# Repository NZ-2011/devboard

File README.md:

# 🔌 DevBoard — RP2040 Development Board

> A compact, open-source development board powered by the **Raspberry Pi RP2040** — featuring a 12 MHz crystal oscillator, onboard 3.3V regulation, QSPI Flash, SWD debug header, and 40 broken-out GPIO pins. Built for makers, students, and engineers who want full control.

---
## DEVBOARD
<!-- 📸 BOARD PHOTO: Replace the line below with your actual board photo -->

> 📷 *3D render and PCB layout available in `/assets/images/`*

# Purpose:
it is like an small computer that can fit in ur hand.you plug it in your computer or Laptop to test the prototype or product ypur makimg.it is used to conmect lights,sensors,mototrs according to the code you write.

# How to use it:
1- install the software.and open it.

2-plug the devboard in ur computer or laptop with a good USB cable (a normal cable will work too)

3-upload ur first program

4-connect real stuff. like LEDs,button etc
(always unplug USB before toiching wires)

# Why did i make it:
we all have to start somehwere to i thought to start my PCB,electronics journey from here.i could have selected something easy but where is the fun in that so i decided to make a devboard.and also during this i learned how to use kicad and how to make a PCB,and some ways to fix errors.

---

##  Features

- 🧠 **Microcontroller:** Raspberry Pi RP2040 (Dual-core ARM Cortex-M0+ @ up to 133MHz)
- 💾 **Flash Memory:** 2MB QSPI Flash (W25Q16)
- ⚡ **Power:** USB-C (USB 2.0, 14P) with onboard MCP1700-3300 LDO (3.3V output)
- 📌 **GPIO:** 40 pins broken out via dual 1×20 pin headers (GPIO0–GPIO29 + power/GND)
- 🔮 **Crystal:** 12 MHz external oscillator for accurate USB & timing
- 🔘 **Button:** 1× tactile push button (SW1 — Boot/User)
- 🛠️ **Debug:** 3-pin SWD header (J4) for hardware debugging
- 📐 **Form Factor:** Compact stick ~55mm × 21mm, Pico-compatible footprint
- 🎨 **PCB:** 2-layer green PCB with black pin headers
- 🔧 **Compatible with:** MicroPython, CircuitPython, Arduino IDE, C/C++ SDK

---

## 📐 SCHEMATIC

## PCB Design

## 3D imagine

## Magazine

| Left Header (J2) | Pin | Pin | Right Header (J3) |
|---|---|---|---|
| GPIO0 | 1 | 1 | GPIO16 |
| GPIO1 | 2 | 2 | GPIO17 |
| GPIO2 | 3 | 3 | GPIO18 |
| GPIO3 | 4 | 4 | GPIO19 |
| GPIO4 | 5 | 5 | GPIO20 |
| GPIO5 | 6 | 6 | GPIO21 |
| GPIO6 | 7 | 7 | GPIO22 |
| GPIO7 | 8 | 8 | GPIO23 |
| GPIO8 | 9 | 9 | GPIO24 |
| GPIO9 | 10 | 10 | GPIO25 |
| GPIO10 | 11 | 11 | GPIO26_ADC0 |
| GPIO11 | 12 | 12 | GPIO27_ADC1 |
| GPIO12 | 13 | 13 | GPIO28_ADC2 |
| GPIO13 | 14 | 14 | GPIO29_ADC3 |
| GPIO14 | 15 | 15 | VBUS (5V) |
| GPIO15 | 16 | 16 | 3V3 |
| RUN | 17 | 17 | GND |
| SWCLK | 18 | 18 | GND |
| SWDIO | 19 | 19 | GND |
| GND | 20 | 20 | GND |

> ⚠️ *GPIO26–29 are also ADC-capable. VBUS is 5V direct from USB — use with caution.*

---

##  Getting Started

### Prerequisites

- [Arduino IDE](https://www.arduino.cc/en/software) **or** [Thonny (MicroPython)](https://thonny.org/) **or** [VS Code + Pico SDK](https://www.raspberrypi.com/documentation/microcontrollers/c_sdk.html)
- USB-C cable
- [RP2040 Arduino Core by Earle Philhower](https://github.com/earlephilhower/arduino-pico) (if using Arduino IDE)

### Flash MicroPython

1. Hold the **BOOT button (SW1)** and plug in USB — the board mounts as a USB drive.
2. Download the latest [MicroPython UF2 for RP2040](https://micropython.org/download/rp2-pico/).
3. Drag and drop the `.uf2` file onto the drive — it reboots automatically.
4. Open **Thonny**, select `MicroPython (Raspberry Pi Pico)` as interpreter.
5. Run your first program:

```python
from machine import Pin
from time import sleep

led = Pin(25, Pin.OUT)  # Adjust to your onboard LED pin if present

while True:
    led.toggle()
    sleep(0.5)
```

### Flash with Arduino IDE

1. In Arduino IDE go to **File > Preferences** and add this URL to Board Manager:
   `https://github.com/earlephilhower/arduino-pico/releases/download/global/package_rp2040_index.json`
2. Go to **Tools > Board > Board Manager**, search `RP2040` and install.
3. Select **Raspberry Pi Pico** (or Generic RP2040) under Tools > Board.
4. Hold BOOT, plug in USB, then upload your sketch.

### SWD Debugging (Advanced)

Connect a **Picoprobe** or **J-Link** to the 3-pin SWD header (J4):

| J4 Pin | Signal |
|---|---|
| 1 | SWCLK |
| 2 | GND |
| 3 | SWDIO |

---

## 📁 Repository Structure

```
devboard/
├── hardware/
│   ├── schematic.pdf        # Full KiCad schematic export
│   ├── gerbers/             # Gerber files for PCB manufacturing
│   ├── bom.csv              # Bill of Materials
│   └── kicad/               # KiCad 6 source files (.kicad_sch, .kicad_pcb)
├── firmware/
│   └── examples/            # MicroPython & Arduino example sketches
├── assets/
│   └── images/              # Board photos, 3D renders, pinout diagrams
├── docs/
│   └── getting-started.md   # Detailed setup guide
├── LICENSE-HARDWARE         # CERN OHL v2-S
├── LICENSE-FIRMWARE         # MIT
└── README.md
```

---

## 🔧 Hardware Files

| File | Description |
|---|---|
| `hardware/schematic.pdf` | Full circuit schematic (KiCad 6.0) |
| `hardware/gerbers/` | Gerber + drill files — tested with JLCPCB & PCBWay |
| `hardware/bom.csv` | Full BOM: W25Q16, MCP1700-3300, 12MHz crystal, passives |
| `hardware/kicad/` | Editable KiCad source files |

**Key ICs used:**
- `U1` — RP2040 (Raspberry Pi)
- `U2` — MCP1700-3300TT (3.3V LDO, 250mA)
- `U4` — W25Q16 (2MB QSPI Flash)
- `Y1` — 12 MHz Crystal Oscillator

---

> 💡 Have an idea? [Open a feature request](https://github.com/NZ-2011/devboard/issues/new?template=feature_request.md)

##Createdwith help of hackclub tutorial.
---

## Contributing

Contributions are what make open source amazing! Here's how you can help:

### Reporting Bugs
1. Check if the issue exists in [Issues](https://github.com/NZ-2011/devboard/issues)
2. Open a new issue with your OS, toolchain version, steps to reproduce, and expected vs actual behavior.

### Submitting Hardware Changes
1. Fork the repo
2. Edit in **KiCad** (same version used for this project)
3. Export updated Gerbers + schematic PDF
4. Submit a Pull Request with a clear description

### Submitting Firmware / Code
1. Fork the repo
2. Create a branch: `git checkout -b feature/your-feature-name`
3. Commit: `git commit -m "Add: description of change"`
4. Push and open a Pull Request

Look for [`good first issue`](https://github.com/NZ-2011/devboard/labels/good%20first%20issue) tags for beginner-friendly tasks!

---

## 📜 License

This project uses two licenses:

- **Firmware & Software** → [MIT License](LICENSE-FIRMWARE) — free to use, modify, and distribute with credit.
- **Hardware (PCB, Schematics)** → [CERN Open Hardware Licence v2 - Strongly Reciprocal](LICENSE-HARDWARE) — open hardware; modifications must also stay open.

---

## 🙌 Acknowledgements

- [Raspberry Pi Foundation](https://www.raspberrypi.com/) for the RP2040 chip and documentation
- [KiCad EDA](https://www.kicad.org/) for open-source PCB design tools
---

<p align="center">⭐ If you find this useful, please star the repo — it helps others discover it!</p>

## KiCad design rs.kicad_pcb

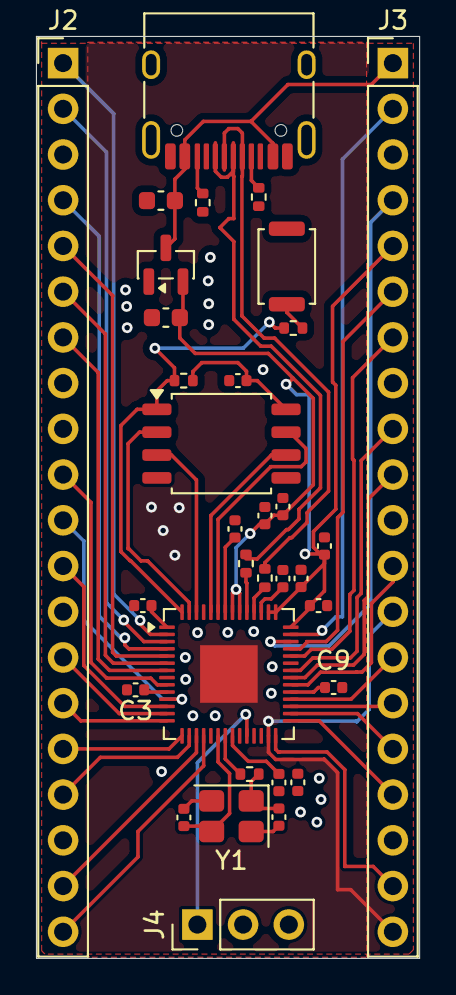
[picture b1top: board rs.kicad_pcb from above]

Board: 2 copper layers, 21.3 x 51.2 mm, 33 parts (0 on the bottom side), 48 nets.

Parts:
C1, C10: 1uF; C_0402_1005Metric
C2, C3, C4, C5, C6, C7, C8, C9, C11, C12, C17: 0.1uF; C_0402_1005Metric
C13, C14: 10uF; C_0603_1608Metric
C15, C16: 33pF; C_0402_1005Metric
J1: USB_C_Receptacle_USB2.0_14P; USB_C_Receptacle_HRO_TYPE-C-31-M-12
J2, J3: Conn_01x20; PinHeader_1x20_P2.54mm_Vertical
J4: Conn_01x03; PinHeader_1x03_P2.54mm_Vertical
R1, R2: 5.1K; R_0402_1005Metric
R3, R4: 27; R_0402_1005Metric
R5, R6: 1K; R_0402_1005Metric
R7: 10K; R_0402_1005Metric
SW1: SW_Push; SW_Push_SPST_NO_Alps_SKRK
U1: RP2040; QFN-56-1EP_7x7mm_P0.4mm_EP3.2x3.2mm
U2: MCP1700x-330xxTT; SOT-23
U4: W25Q16JVUXIQ TR; SOIC-8_5.3x5.3mm_P1.27mm
Y1: 12 MHz; Crystal_SMD_3225-4Pin_3.2x2.5mm

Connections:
+1V1: C10.1, C11.1, C12.1, U1.23 (DVDD), U1.45 (VREG_VOUT), U1.50 (DVDD)
+3V3: C1.1, C2.1, C3.1, C4.1, C5.1, C6.1, C7.1, C8.1, C9.1, C14.1, C17.1, J3.5, R7.1, U1.1 (IOVDD), U1.10 (IOVDD), U1.22 (IOVDD), U1.33 (IOVDD), U1.42 (IOVDD), U1.43 (ADC_AVDD), U1.44 (VREG_VIN), U1.48 (USB_VDD), U1.49 (IOVDD), U2.2 (VO), U4.8 (VCC)
/GPIO0: J2.1, U1.2 (GPIO0)
/GPIO1: J2.2, U1.3 (GPIO1)
/GPIO2: J2.4, U1.4 (GPIO2)
/GPIO3: J2.5, U1.5 (GPIO3)
/GPIO4: J2.6, U1.6 (GPIO4)
/GPIO5: J2.7, U1.7 (GPIO5)
/GPIO6: J2.9, U1.8 (GPIO6)
/GPIO7: J2.10, U1.9 (GPIO7)
/GPIO8: J2.11, U1.11 (GPIO8)
/GPIO9: J2.12, U1.12 (GPIO9)
/GPIO10: J2.14, U1.13 (GPIO10)
/GPIO11: J2.15, U1.14 (GPIO11)
/GPIO12: J2.16, U1.15 (GPIO12)
/GPIO13: J2.17, U1.16 (GPIO13)
/GPIO14: J2.19, U1.17 (GPIO14)
/GPIO15: J2.20, U1.18 (GPIO15)
/GPIO17: J3.19, U1.28 (GPIO17)
/GPIO18: J3.17, U1.29 (GPIO18)
/GPIO19: J3.16, U1.30 (GPIO19)
/GPIO20: J3.15, U1.31 (GPIO20)
/GPIO21: J3.14, U1.32 (GPIO21)
/GPIO22: J3.12, U1.34 (GPIO22)
/GPIO23: J3.10, U1.35 (GPIO23)
/GPIO24: J3.9, U1.36 (GPIO24)
/GPIO26_ADC0: J3.7, U1.38 (GPIO26/ADC0)
/GPIO27_ADC1: J3.6, U1.39 (GPIO27/ADC1)
/GPIO28_ADC2: J3.4, U1.40 (GPIO28/ADC2)
/GPIO29_ADC3: J3.2, U1.41 (GPIO29/ADC3)
/QSPI_SCLK: U1.52 (QSPI_SCLK), U4.6 (CLK)
/QSPI_SD1: U1.55 (QSPI_SD1), U4.2 (DO/IO_{1})
/QSPI_SD2: U1.54 (QSPI_SD2), U4.3 (~WP/IO_{2})
/QSPI_SD3: U1.51 (QSPI_SD3), U4.7 (~HOLD/~RESET/IO_{3})
/QSPI_SS: R6.1, R7.2, U1.56 (~QSPI_SS), U4.1 (~CS)
/SWCLK: J4.1, U1.24 (SWCLK)
/USB_D+: J1.A6 (D+), J1.B6 (D+), R3.1
/USB_D-: J1.A7 (D-), J1.B7 (D-), R4.1
/XIN: C15.2, U1.20 (XIN), Y1.3
/XOUT: R5.2, U1.21 (XOUT)
GND: C1.2, C2.2, C3.2, C4.2, C5.2, C6.2, C7.2, C8.2, C9.2, C10.2, C11.2, C12.2, C13.2, C14.2, C15.1, C16.1, C17.2, J1.A1 (GND), J1.A12 (GND), J1.B1 (GND), J1.B12 (GND), J1.SH (SHIELD), J2.3, J2.8, J2.13, J2.18, J3.3, J3.8, J3.13, J3.18, J3.20, J4.2, R1.2, R2.2, SW1.1, U1.19 (TESTEN), U1.27 (GPIO16), U1.57 (GND), U2.1 (GND), U4.4 (GND), Y1.2 (G), Y1.4 (G)
unnamed: C16.2, R5.1, Y1.1
unnamed: J1.A5 (CC1), R2.1
unnamed: J1.B5 (CC2), R1.1
unnamed: R6.2, SW1.2
unnamed: R4.2, U1.46 (USB_DM)
unnamed: R3.2, U1.47 (USB_DP)
VBUS: C13.1, J1.A4 (VBUS), J1.A9 (VBUS), J1.B4 (VBUS), J1.B9 (VBUS), J3.1, U2.3 (VI)

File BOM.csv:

"Id";"Designator";"Footprint";"Quantity";"Designation";"Supplier and ref";
1;"C1, C10";"C_0402_1005Metric";2;"1uF";;;
2;"C2, C3, C4, C5, C6, C7, C8, C9, C11, C12, C17";"C_0402_1005Metric";11;"0.1uF";;;
3;"C13, C14";"C_0603_1608Metric";2;"10uF";;;
4;"C15, C16";"C_0402_1005Metric";2;"33pF";;;
5;"J1";"USB_C_Receptacle_HRO_TYPE-C-31-M-12";1;"USB_C_Receptacle_USB2.0_14P";;;
6;"J2, J3";"PinHeader_1x20_P2.54mm_Vertical";2;"Conn_01x20";;;
7;"J4";"PinHeader_1x03_P2.54mm_Vertical";1;"Conn_01x03";;;
8;"R1, R2";"R_0402_1005Metric";2;"5.1K";;;
9;"R3, R4";"R_0402_1005Metric";2;"27";;;
10;"R5, R6";"R_0402_1005Metric";2;"1K";;;
11;"R7";"R_0402_1005Metric";1;"10K";;;
12;"SW1";"SW_Push_SPST_NO_Alps_SKRK";1;"SW_Push";;;
13;"U1";"QFN-56-1EP_7x7mm_P0.4mm_EP3.2x3.2mm";1;"RP2040";;;
14;"U2";"SOT-23";1;"MCP1700x-330xxTT";;;
15;"U4";"SOIC-8_5.3x5.3mm_P1.27mm";1;"W25Q16JVUXIQ TR";;;
16;"Y1";"Crystal_SMD_3225-4Pin_3.2x2.5mm";1;"12 MHz";;;

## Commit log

2026-06-08 Add Magazine section to README
    Added a new section for Magazine with an image.
2026-06-08 added magazine
2026-06-08 added magazine cover with qr code
2026-06-08 updated magazine pic
2026-06-08 added BOM
2026-06-09 addded bom

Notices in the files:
README.md:
License: MIT
Hardware License
